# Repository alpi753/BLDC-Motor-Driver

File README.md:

# BLDC Motor Driver

Open-source BLDC ESC firmware for STM32 targets plus a desktop telemetry console. The repo contains KiCad hardware designs, two firmware builds (STM32F411 and STM32G431), and an Electron dashboard that decodes live motor data over USB.

Part of the broader [BLDC-Motor-Driver](https://github.com/alpi753/BLDC-Motor-Driver) project.

## Repository layout

```
PCB/
├── hardware/              KiCad schematics and PCBs (ESC, MCU, MOSFET boards)
├── software/
│   ├── console/           Electron + React telemetry dashboard
│   ├── stm32f411/         STM32F411CE firmware (CubeMX + CMake)
│   ├── stm32g431/         STM32G431CB firmware (CubeMX + CMake)
│   ├── shared/bsp/        Shared motor control, telemetry, USB/CBOR, DroneCAN
│   └── scripts/           Host-side utilities (e.g. telem_reader.py)
└── AGENTS.md              Contributor and AI-agent guide (architecture, protocol, gaps)
```

## Quick start

### Console (dashboard)

```bash
cd software/console
npm install
npm run dev
```

Linux USB serial access usually requires membership in the `dialout` group:

```bash
sudo usermod -a -G dialout $USER   # re-login required
```

### Firmware

Prerequisites: `arm-none-eabi-gcc`, `cmake`, `ninja` (and `openocd` for flashing).

**STM32F411**

```bash
cd software/stm32f411
cmake --preset Debug
cmake --build --preset Debug
make flash    # optional — ST-Link + OpenOCD
```

**STM32G431**

```bash
cd software/stm32g431
cmake --preset Debug
cmake --build --preset Debug
make flash
```

Select the board at configure time with `-DBLDC_BOARD=stm32f411` or `-DBLDC_BOARD=stm32g431` (default is `stm32g431` in the shared BSP CMake).

DroneCAN DSDL codegen (first build only, if `dsdl_generated/` is missing):

```bash
cd software/stm32f411   # or stm32g431
make dsdl_gen_build
```

## How it fits together

```
┌─────────────────────┐     USB CDC 115200 baud      ┌──────────────────────┐
│  STM32F411 / G431   │  CBOR [type, payload]        │  Electron main       │
│  TelemThread (~1Hz) │ ───────────────────────────► │  serial.ts decoder   │
│                     │ ◄─────────────────────────── │  ipc → React cards   │
└─────────────────────┘   settings CBOR (RX only)   └──────────────────────┘
         │
         ├── TIM1 complementary PWM → DRV8323 → 3-phase bridge
         ├── SPI1 → DRV8323R (enable, faults, gain, OC)
         └── ADC → phase currents, bus voltage, NTC temperature
```

Connect the board over USB, open the console, pick the CDC serial port, and dashboard cards update from live telemetry.

## Telemetry today

Both boards publish the same CBOR telemetry map when `CONFIG_BLDC_TELEM_USE_DEMO=n` (current default on both).

| Data | F411 | G431 |
|------|------|------|
| Phase currents (`i_a`–`i_c`) | Real — ADC1 DMA, PA0–PA2 | Real — ADC1 injected, PA0–PA2 |
| Bus voltage (`v_bat`) | Real — PA5 (`ADC1_IN5`) | Real — PB2 (`ADC2_IN12`) |
| Phase voltages (`v_a`–`v_c`) | Real — PWM duty × Vbus | Real — PWM duty × Vbus |
| FET temperature (`temp`) | Real — PA6 NTC, IIR filtered | Real — PA6 NTC, IIR + CORDIC/FMAC |
| Energy used (`e_used`) | Real — integrated V×I | Real — integrated V×I |
| Battery current (`i_bat`) | Approx — mean \|phase currents\| | Same |
| RPM, FOC (`i_d`/`i_q`), angles, observer fields | Stubbed 0 | Stubbed 0 |
| Energy remaining (`e_rem`) | Always 0 | Always 0 |
| Motor NTC (PA7) | Sampled, not telemetered | Sampled, not telemetered |

Telemetry rate is about **1 Hz** (one CBOR frame per second from `TelemThread`).

## What's not done yet

- Sensorless FOC and speed/position observers (RPM, angles, `i_d`/`i_q` stay at zero)
- Console settings UI → firmware settings over CBOR
- DroneCAN on the wire (libcanard layer exists; CAN HAL TX/RX not hooked up)
- `energy_rem` from battery capacity

For UI development without hardware, set `CONFIG_BLDC_TELEM_USE_DEMO=y` in the target's `software/shared/bsp/boards/<board>/board.conf` and rebuild.

## Documentation

- **[AGENTS.md](AGENTS.md)** — Full architecture, protocol reference, board differences, coding rules, and common tasks for contributors and AI agents.
- **[software/console/README.md](software/console/README.md)** — Console-specific setup, IPC API, and UI structure.

## License

No root-level LICENSE file is present yet. Check individual components and submodules for their terms.

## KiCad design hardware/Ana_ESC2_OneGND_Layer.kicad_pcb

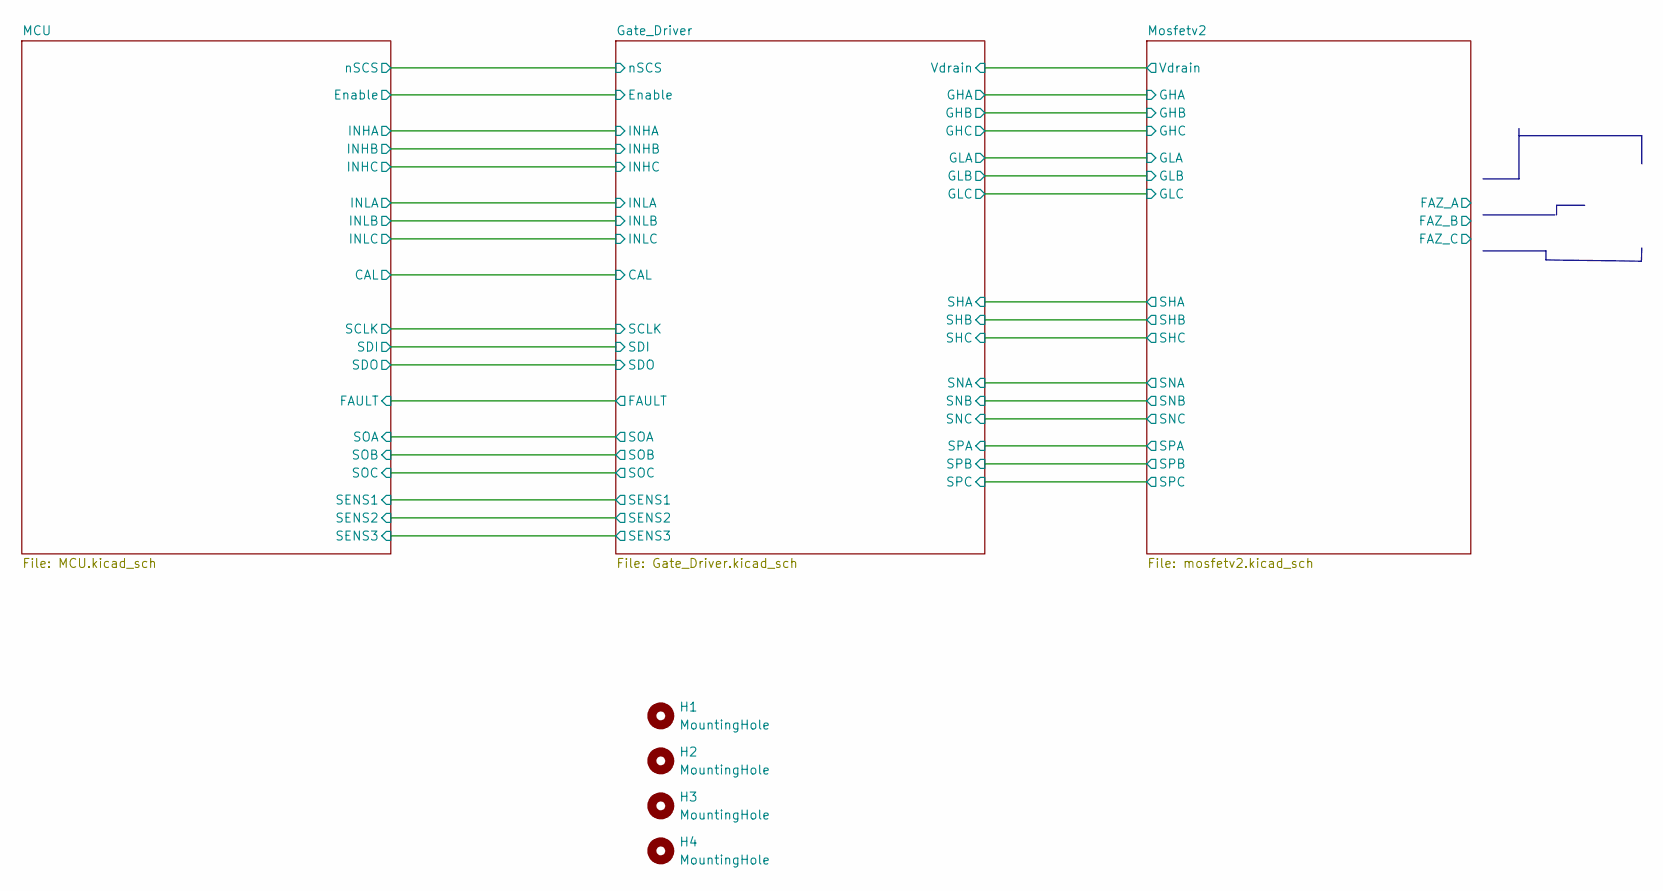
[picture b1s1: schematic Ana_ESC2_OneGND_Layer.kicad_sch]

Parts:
H1, H2, H3, H4: MountingHole; MountingHole_3.2mm_M3

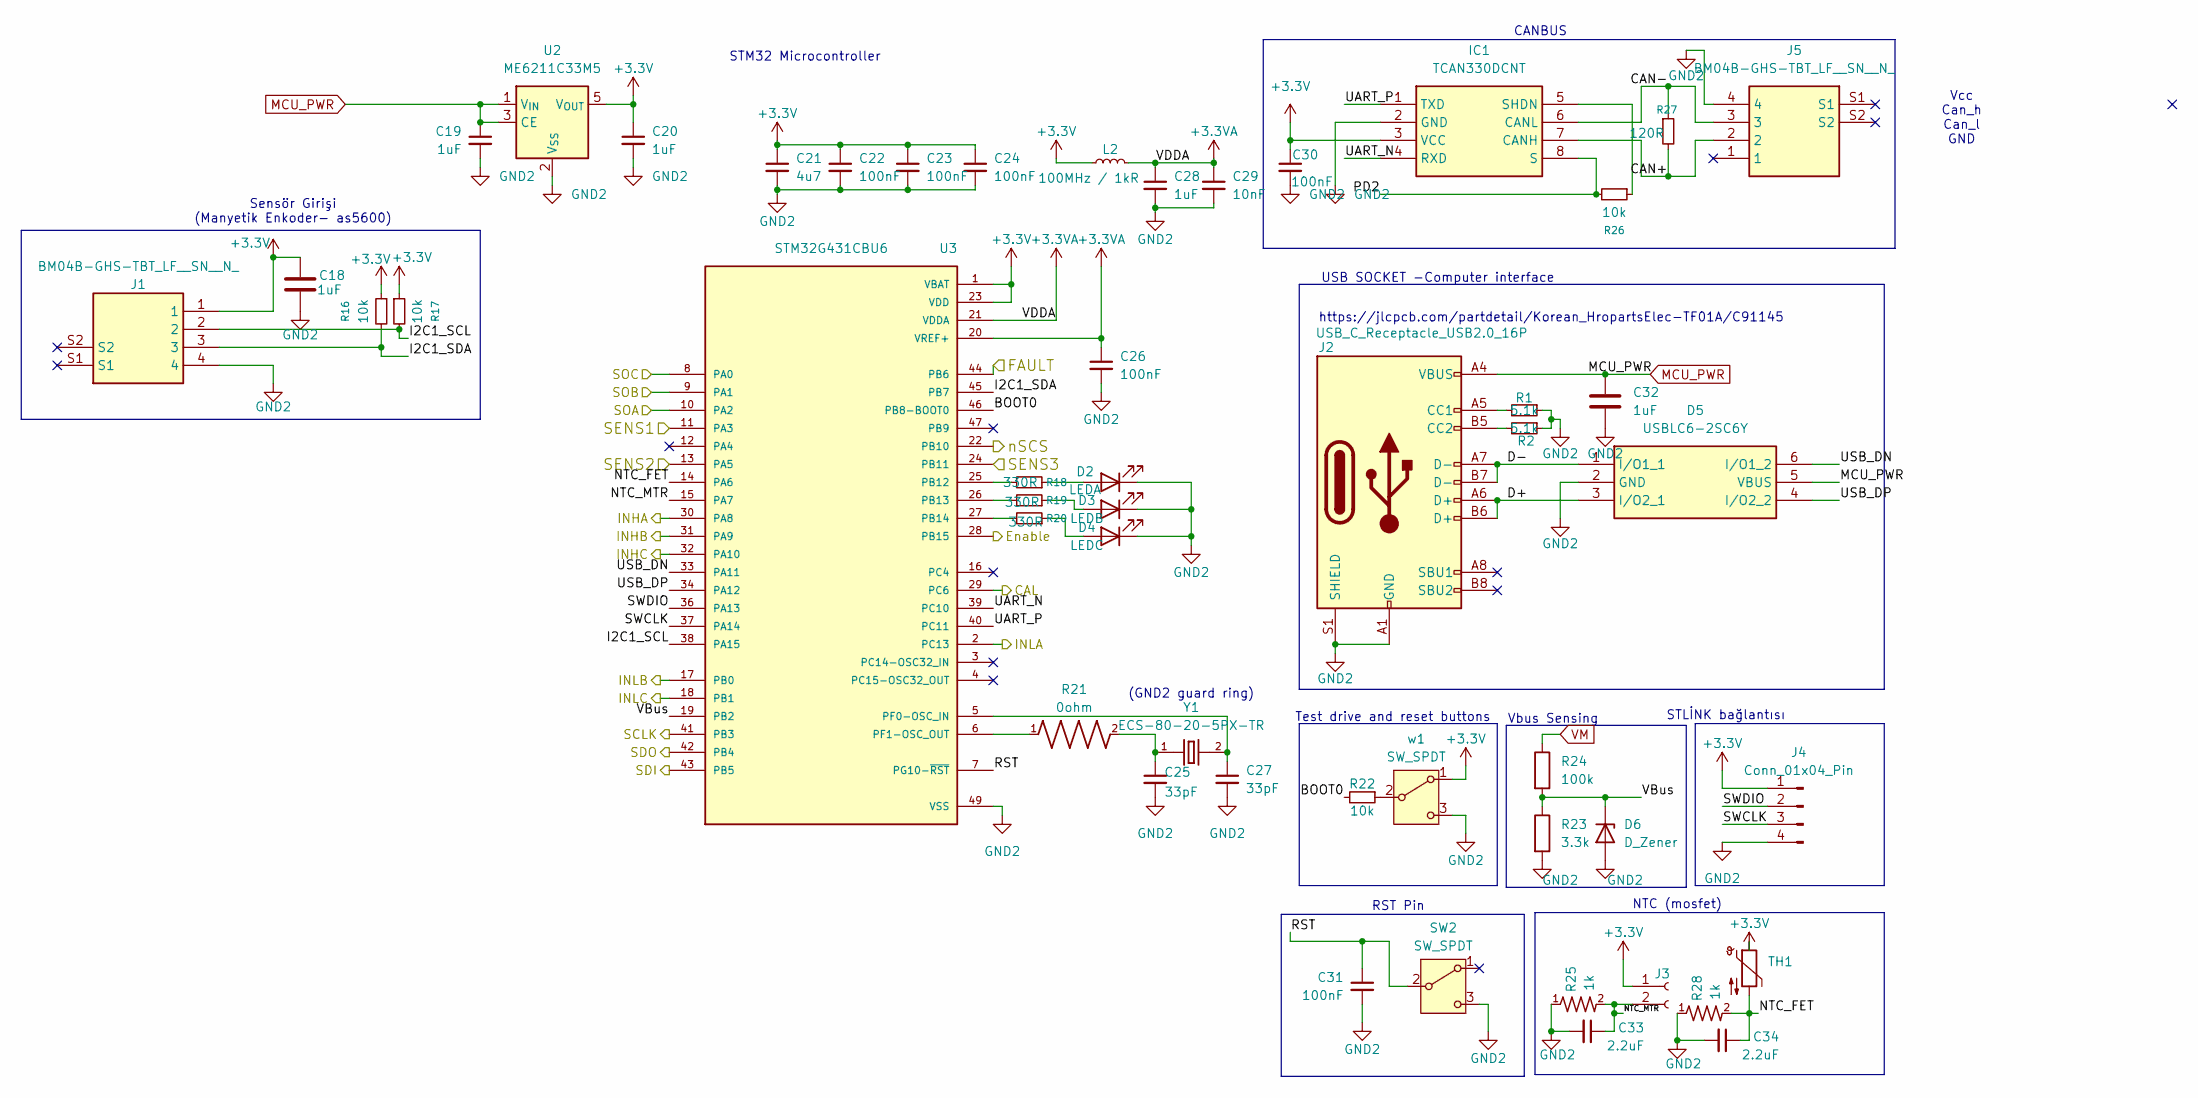
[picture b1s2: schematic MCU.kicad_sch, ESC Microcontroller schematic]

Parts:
C18, C32: 1uF; C_0603_1608Metric_Pad1.08x0.95mm_HandSolder
C19, C20, C28: 1uF; C_0603_1608Metric_Pad1.08x0.95mm_HandSolder; LCSC Part # C52923
C21: 4u7; C_0603_1608Metric_Pad1.08x0.95mm_HandSolder; LCSC Part # C19666
C22, C23, C24, C26, C31: 100nF; C_0603_1608Metric_Pad1.08x0.95mm_HandSolder; LCSC Part # C1525
C25, C27: 33pF; C_0603_1608Metric_Pad1.08x0.95mm_HandSolder
C29: 10nF; C_0603_1608Metric_Pad1.08x0.95mm_HandSolder; LCSC Part # C15195
C30: 100nF; C_0603_1608Metric_Pad1.08x0.95mm_HandSolder
C33, C34: 2.2uF; C_0603_1608Metric_Pad1.08x0.95mm_HandSolder
D2: LEDA; LED_0603_1608Metric_Pad1.05x0.95mm_HandSolder
D3: LEDB; LED_0603_1608Metric_Pad1.05x0.95mm_HandSolder
D4: LEDC; LED_0603_1608Metric_Pad1.05x0.95mm_HandSolder
D5: USBLC6-2SC6Y; SOT95P280X145-6N; Manufacturer_Part_Number USBLC6-2SC6Y; Mouser Part Number 511-USBLC6-2SC6Y
D6: D_Zener; SOD3716X135N
IC1: TCAN330DCNT; SOT65P280X145-8N; Manufacturer_Part_Number TCAN330DCNT; Mouser Part Number 595-TCAN330DCNT
J1, J5: BM04B-GHS-TBT_LF__SN__N_; JST_BM04B-GHS-TBT_LF__SN__N_; Manufacturer_Part_Number BM04B-GHS-TBT(LF)(SN)(N); Mouser Part Number N/A
J2: USB_C_Receptacle_USB2.0_16P; USB_C_Receptacle_GCT_USB4105-xx-A_16P_TopMnt_Horizontal
J3: Conn_01x02_Socket; TerminalBlock_MaiXu_MX126-5.0-02P_1x02_P5.00mm
J4: Conn_01x04_Pin; PinHeader_1x04_P1.00mm_Vertical
L2: 100MHz / 1kR; L_0603_1608Metric_Pad1.05x0.95mm_HandSolder; LCSC Part # C26443
R1, R2: 5.1k; R_0603_1608Metric_Pad0.98x0.95mm_HandSolder; LCSC Part # C25744
R16, R17, R26: 10k; R_0603_1608Metric_Pad0.98x0.95mm_HandSolder
R18, R19, R20: 330R; R_0603_1608Metric_Pad0.98x0.95mm_HandSolder
R21: 0ohm; RESC1508X55N
R22: 10k; R_0603_1608Metric_Pad0.98x0.95mm_HandSolder; LCSC Part # C25744
R23: 3.3k; R_0603_1608Metric_Pad0.98x0.95mm_HandSolder
R24: 100k; R_0603_1608Metric_Pad0.98x0.95mm_HandSolder
R25, R28: 1k; R_0603_1608Metric_Pad0.98x0.95mm_HandSolder; DigiKey_Part_Number RNCP0603FTD1K00CT-ND
R27: 120R; R_0603_1608Metric_Pad0.98x0.95mm_HandSolder
SW2: SW_SPDT; SW_SPDT_PCM12
TH1: ERT-J1VG103FA; R_0603_1608Metric
U2: ME6211C33M5; SOT-23-5
U3: STM32G431CBU6; QFN50P700X700X60-49N; PARTREV 6
Y1: ECS-80-20-5PX-TR; XTAL_ECS-80-20-5PX-TR; PARTREV 2017
w1: SW_SPDT; SW_SPDT_PCM12

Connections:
+3.3V: C18.1, C20.1, C21.1, C22.1, C23.1, C24.1, C30.1, IC1.3 (VCC), J1.1, J3.1, J4.1, L2.1, R16.1, R17.1, TH1.1, U2.5 (V_{OUT}), U3.1 (VBAT), U3.23 (VDD), U3.35 (VDD), U3.48 (VDD), w1.1 (A); also elsewhere on the board
+3.3VA: C26.1, C28.1, C29.1, L2.2, U3.20 (VREF+), U3.21 (VDDA)
/Gate_Driver/CAL: U3.29 (PC6); also elsewhere on the board
/Gate_Driver/Enable: U3.28 (PB15); also elsewhere on the board
/Gate_Driver/INHA: U3.30 (PA8); also elsewhere on the board
/Gate_Driver/INHB: U3.31 (PA9); also elsewhere on the board
/Gate_Driver/INHC: U3.32 (PA10); also elsewhere on the board
/Gate_Driver/INLA: U3.2 (PC13); also elsewhere on the board
/Gate_Driver/INLB: U3.17 (PB0); also elsewhere on the board
/Gate_Driver/INLC: U3.18 (PB1); also elsewhere on the board
/Gate_Driver/SCLK: U3.41 (PB3); also elsewhere on the board
/Gate_Driver/SDI: U3.43 (PB5); also elsewhere on the board
/Gate_Driver/SENS1: U3.11 (PA3); also elsewhere on the board
/Gate_Driver/SENS2: U3.13 (PA5); also elsewhere on the board
/Gate_Driver/SENS3: U3.24 (PB11); also elsewhere on the board
/Gate_Driver/SOA: U3.10 (PA2); also elsewhere on the board
/Gate_Driver/SOB: U3.9 (PA1); also elsewhere on the board
/Gate_Driver/SOC: U3.8 (PA0); also elsewhere on the board
/Gate_Driver/nSCS: U3.22 (PB10); also elsewhere on the board
/MCU/BOOT0: R22.2, U3.46 (PB8-BOOT0)
/MCU/CAN+: IC1.7 (CANH), J5.2, R27.2
/MCU/CAN-: IC1.6 (CANL), J5.3, R27.1
/MCU/D+: D5.3 (I/O2_1), J2.A6 (D+), J2.B6 (D+)
/MCU/D-: D5.1 (I/O1_1), J2.A7 (D-), J2.B7 (D-)
/MCU/I2C1_SCL: J1.2, R17.2, U3.38 (PA15)
/MCU/I2C1_SDA: J1.3, R16.2, U3.45 (PB7)
/MCU/NTC_FET: C34.1, R28.2, TH1.2, U3.14 (PA6)
/MCU/NTC_MTR: C33.1, J3.2, R25.2, U3.15 (PA7)
/MCU/PD2: IC1.8 (S), R26.2
/MCU/RST: C31.1, SW2.2 (B), U3.7 (PG10-~RST)
/MCU/SWCLK: J4.3, U3.37 (PA14)
/MCU/SWDIO: J4.2, U3.36 (PA13)
/MCU/UART_N: IC1.4 (RXD), U3.39 (PC10)
/MCU/UART_P: IC1.1 (TXD), U3.40 (PC11)
/MCU/USB_DN: D5.6 (I/O1_2), U3.33 (PA11)
/MCU/USB_DP: D5.4 (I/O2_2), U3.34 (PA12)
MCU_PWR: C19.1, C32.1, D5.5 (VBUS), J2.A4 (VBUS), J2.A9 (VBUS), J2.B4 (VBUS), J2.B9 (VBUS), U2.1 (V_{IN}), U2.3 (CE); also elsewhere on the board
unnamed: C25.1, R21.2, Y1.1
unnamed: D2.2 (A), R18.1
unnamed: D3.2 (A), R19.1
unnamed: D4.2 (A), R20.1
unnamed: IC1.5 (SHDN), R26.1
unnamed: J2.A5 (CC1), R1.2
unnamed: J2.B5 (CC2), R2.2
unnamed: R18.2, U3.25 (PB12)
unnamed: R19.2, U3.26 (PB13)
unnamed: R20.2, U3.27 (PB14)
unnamed: C27.1, U3.5 (PF0-OSC_IN), Y1.2
unnamed: R21.1, U3.6 (PF1-OSC_OUT)
unnamed: R22.1, w1.2 (B)
VM: R24.1; also elsewhere on the board

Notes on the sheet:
STM32 Microcontroller
Test drive and reset buttons
NTC (mosfet)
(GND2 guard ring)
Sensör Girişi (Manyetik Enkoder- as5600)
STLİNK bağlantısı
CANBUS
https://jlcpcb.com/partdetail/Korean_HropartsElec-TF01A/C91145
USB SOCKET -Computer interface
RST Pin
Vcc Can_h Can_l GND
Vbus Sensing

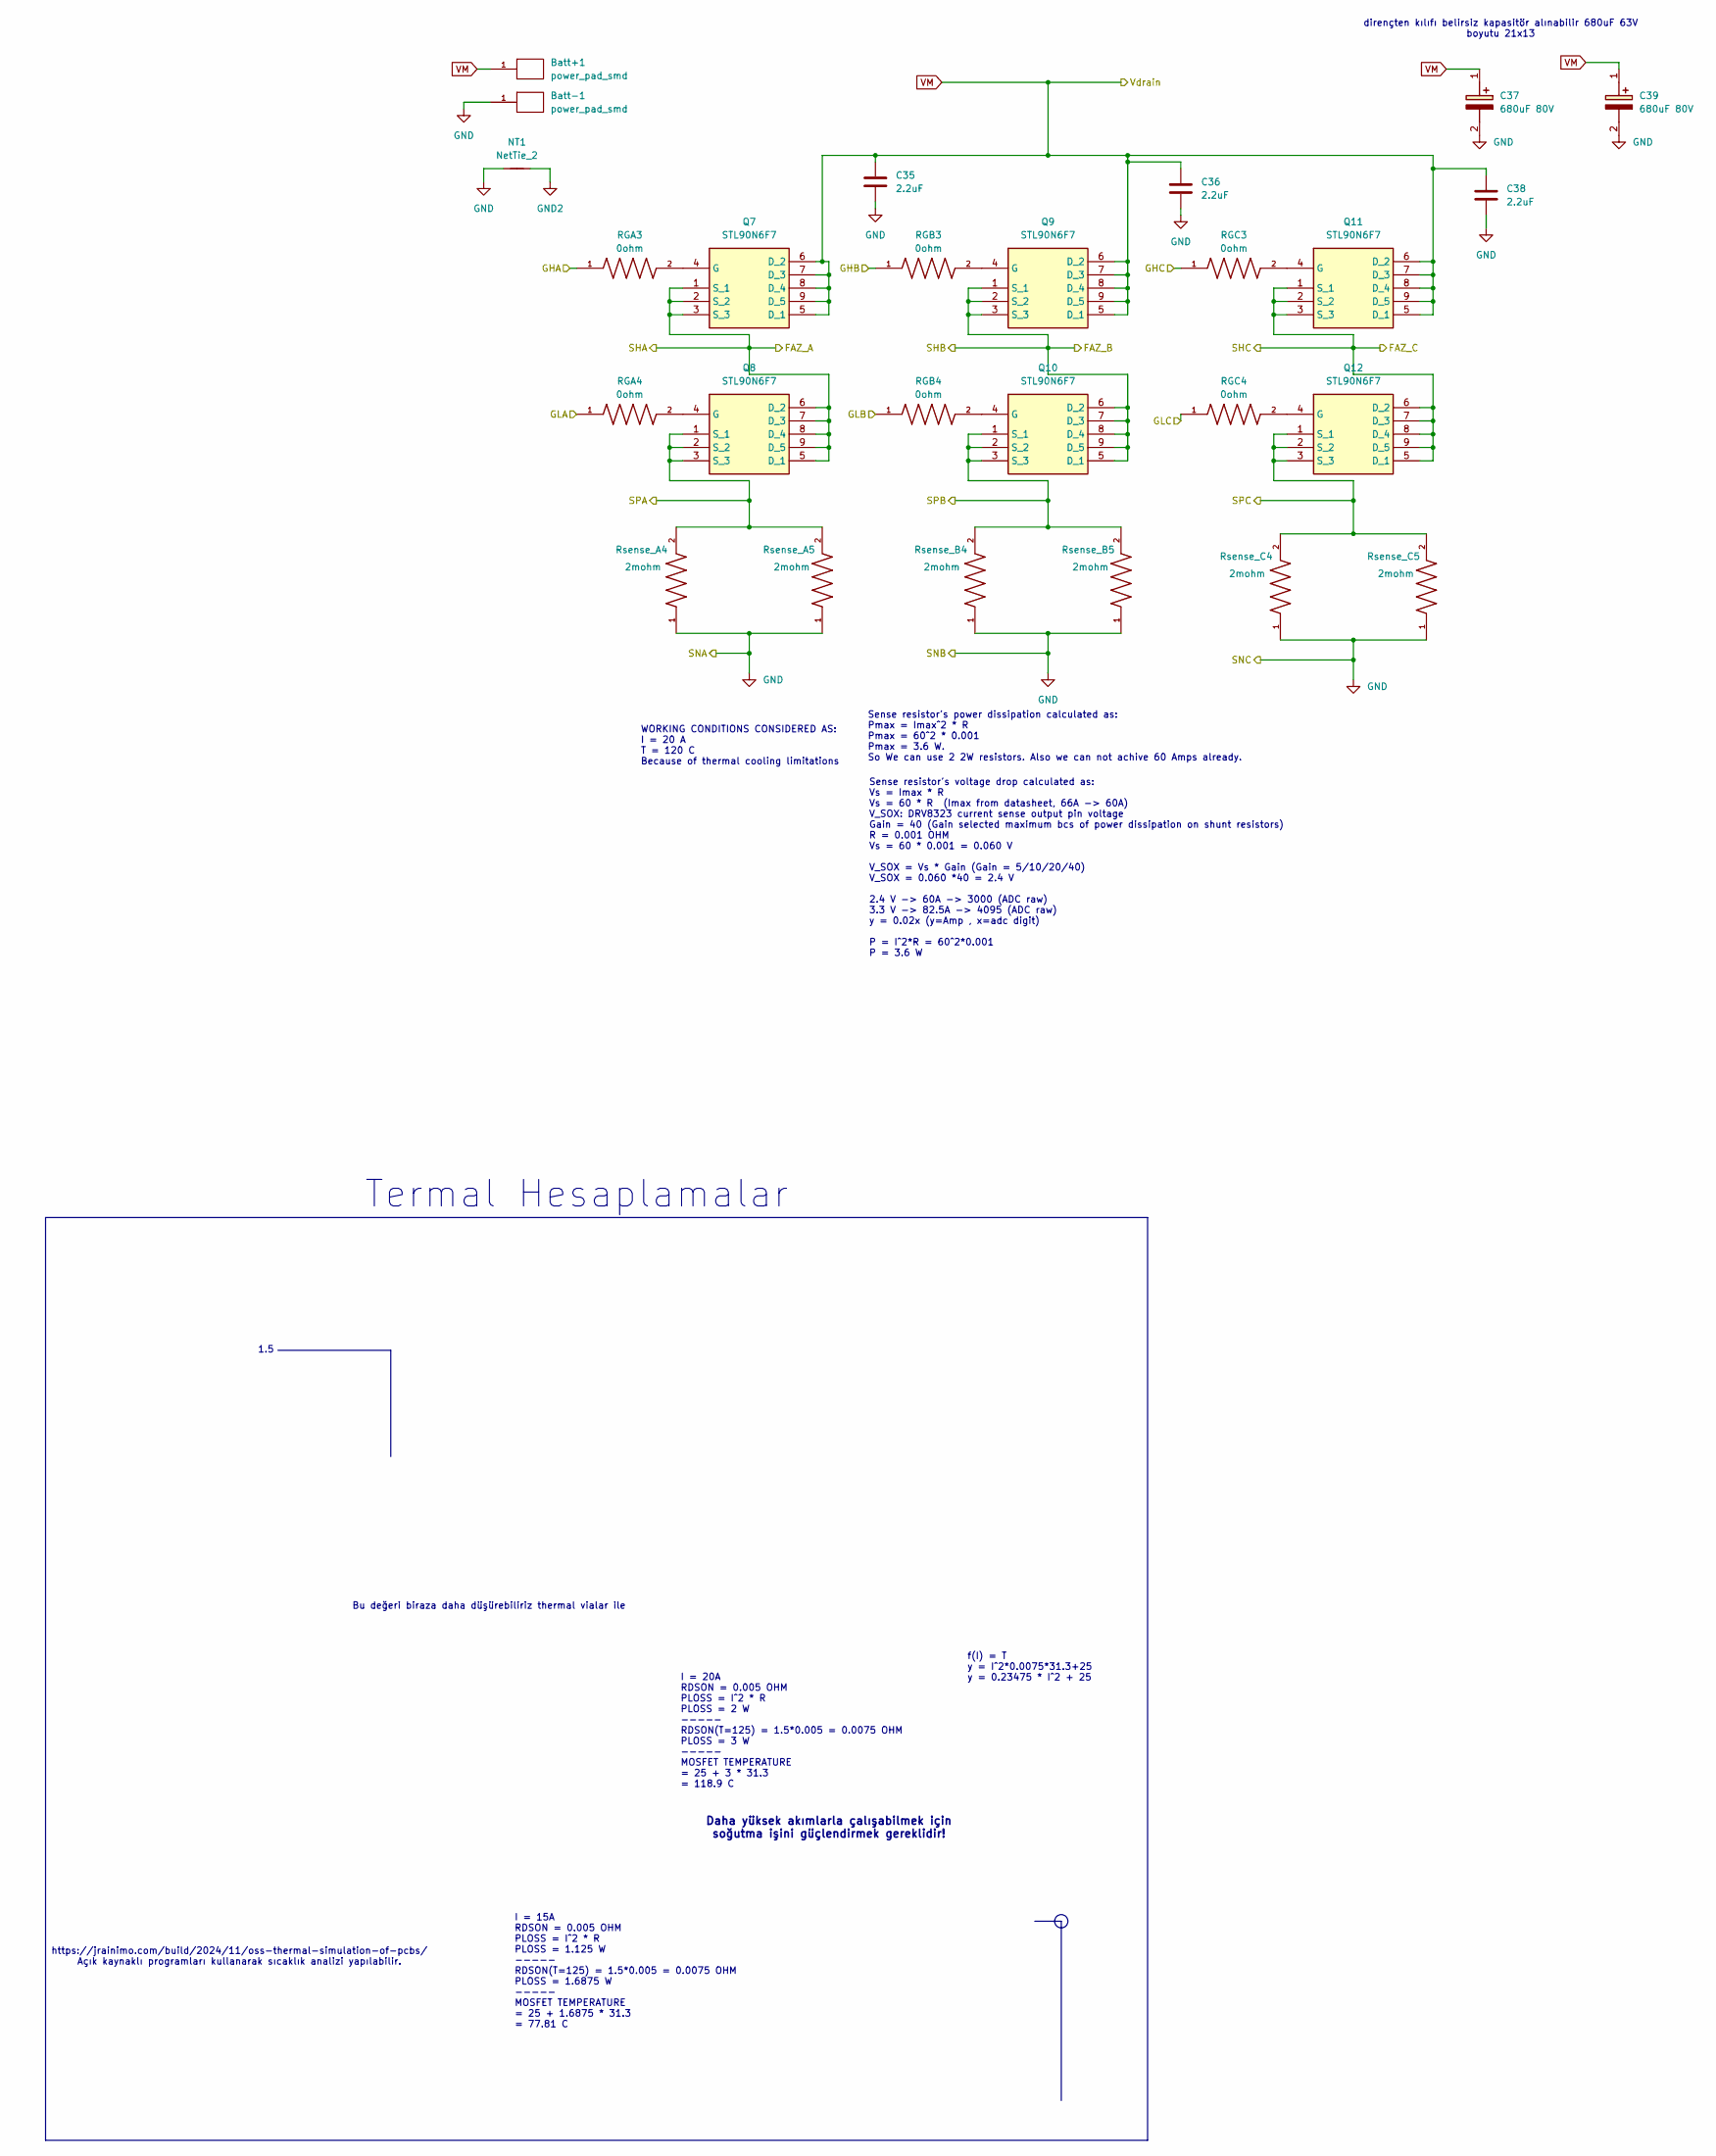
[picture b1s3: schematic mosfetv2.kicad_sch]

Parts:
Batt+1: power_pad_smd; Power_pad_smd
Batt-1: power_pad_smd; Power_pad_smd
C35, C36, C38: 2.2uF; C_0603_1608Metric_Pad1.08x0.95mm_HandSolder
C37, C39: 680uF 80V; CAPPRD750W85D1600H2700; Manufacturer_Part_Number EEUFS1K681
NT1: NetTie_2; NetTie-2_THT_Pad0.3mm
Q7, Q8, Q9, Q10, Q11, Q12: STL90N6F7; STL90N6F7_Thermal_Vias; Manufacturer_Part_Number STL90N6F7; Mouser Part Number 511-STL90N6F7
RGA3, RGA4: 0ohm; RESC1508X55N
RGB3, RGB4: 0ohm; RESC1508X55N
RGC3, RGC4: 0ohm; RESC1508X55N
Rsense_A4, Rsense_A5: 2mohm; RESC6432X80N
Rsense_B4, Rsense_B5: 2mohm; RESC6432X80N
Rsense_C4, Rsense_C5: 2mohm; RESC6432X80N

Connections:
/Gate_Driver/GHA: RGA3.1; also elsewhere on the board
/Gate_Driver/GHB: RGB3.1; also elsewhere on the board
/Gate_Driver/GHC: RGC3.1; also elsewhere on the board
/Gate_Driver/GLA: RGA4.1; also elsewhere on the board
/Gate_Driver/GLB: RGB4.1; also elsewhere on the board
/Gate_Driver/GLC: RGC4.1; also elsewhere on the board
/Gate_Driver/SHA: Q7.1 (S_1), Q7.2 (S_2), Q7.3 (S_3), Q8.5 (D_1), Q8.6 (D_2), Q8.7 (D_3), Q8.8 (D_4), Q8.9 (D_5); also elsewhere on the board
/Gate_Driver/SHB: Q9.1 (S_1), Q9.2 (S_2), Q9.3 (S_3), Q10.5 (D_1), Q10.6 (D_2), Q10.7 (D_3), Q10.8 (D_4), Q10.9 (D_5); also elsewhere on the board
/Gate_Driver/SHC: Q11.1 (S_1), Q11.2 (S_2), Q11.3 (S_3), Q12.5 (D_1), Q12.6 (D_2), Q12.7 (D_3), Q12.8 (D_4), Q12.9 (D_5); also elsewhere on the board
/Gate_Driver/SPA: Q8.1 (S_1), Q8.2 (S_2), Q8.3 (S_3), Rsense_A4.2, Rsense_A5.2; also elsewhere on the board
/Gate_Driver/SPB: Q10.1 (S_1), Q10.2 (S_2), Q10.3 (S_3), Rsense_B4.2, Rsense_B5.2; also elsewhere on the board
/Gate_Driver/SPC: Q12.1 (S_1), Q12.2 (S_2), Q12.3 (S_3), Rsense_C4.2, Rsense_C5.2; also elsewhere on the board
unnamed: Q7.4 (G), RGA3.2
unnamed: Q8.4 (G), RGA4.2
unnamed: Q9.4 (G), RGB3.2
unnamed: Q10.4 (G), RGB4.2
unnamed: Q11.4 (G), RGC3.2
unnamed: Q12.4 (G), RGC4.2
VM: Batt+1.1, C35.1, C36.1, C37.1 (+), C38.1, C39.1 (+), Q7.5 (D_1), Q7.6 (D_2), Q7.7 (D_3), Q7.8 (D_4), Q7.9 (D_5), Q9.5 (D_1), Q9.6 (D_2), Q9.7 (D_3), Q9.8 (D_4), Q9.9 (D_5), Q11.5 (D_1), Q11.6 (D_2), Q11.7 (D_3), Q11.8 (D_4), Q11.9 (D_5); also elsewhere on the board

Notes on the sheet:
https://jrainimo.com/build/2024/11/oss-thermal-simulation-of-pcbs/ Açık kaynaklı programları kullanarak sıcaklık analizi yapılabilir.
Daha yüksek akımlarla çalışabilmek için soğutma işini güçlendirmek gereklidir!
I = 20A RDSON = 0.005 OHM PLOSS = I^2 * R PLOSS = 2 W ----- RDSON(T=125) = 1.5*0.005 = 0.0075 OHM PLOSS = 3 W ----- MOSFET TEMPERATURE = 25 + 3 * 31.3 = 118.9 C
1.5
f(I) = T y = I^2*0.0075*31.3+25 y = 0.23475 * I^2 + 25
Sense resistor's power dissipation calculated as: Pmax = Imax^2 * R Pmax = 60^2 * 0.001 Pmax = 3.6 W. So We can use 2 2W resistors. Also we can not achive 60 Amps already.
Termal Hesaplamalar
dirençten kılıfı belirsiz kapasitör alınabilir 680uF 63V boyutu 21x13
Sense resistor's voltage drop calculated as: Vs = Imax * R Vs = 60 * R (Imax from datasheet, 66A -> 60A) V_SOX: DRV8323 current sense output pin voltage Gain = 40 (Gain selected maximum bcs of power dissipation on shunt resistors) R = 0.001 OHM Vs = 60 * 0.001 = 0.060 V V_SOX = Vs * Gain (Gain = 5/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
WORKING CONDITIONS CONSIDERED AS: I = 20 A T = 120 C Because of thermal cooling limitations
I = 15A RDSON = 0.005 OHM PLOSS = I^2 * R PLOSS = 1.125 W ----- RDSON(T=125) = 1.5*0.005 = 0.0075 OHM PLOSS = 1.6875 W ----- MOSFET TEMPERATURE = 25 + 1.6875 * 31.3 = 77.81 C
Bu değeri biraza daha düşürebiliriz thermal vialar ile

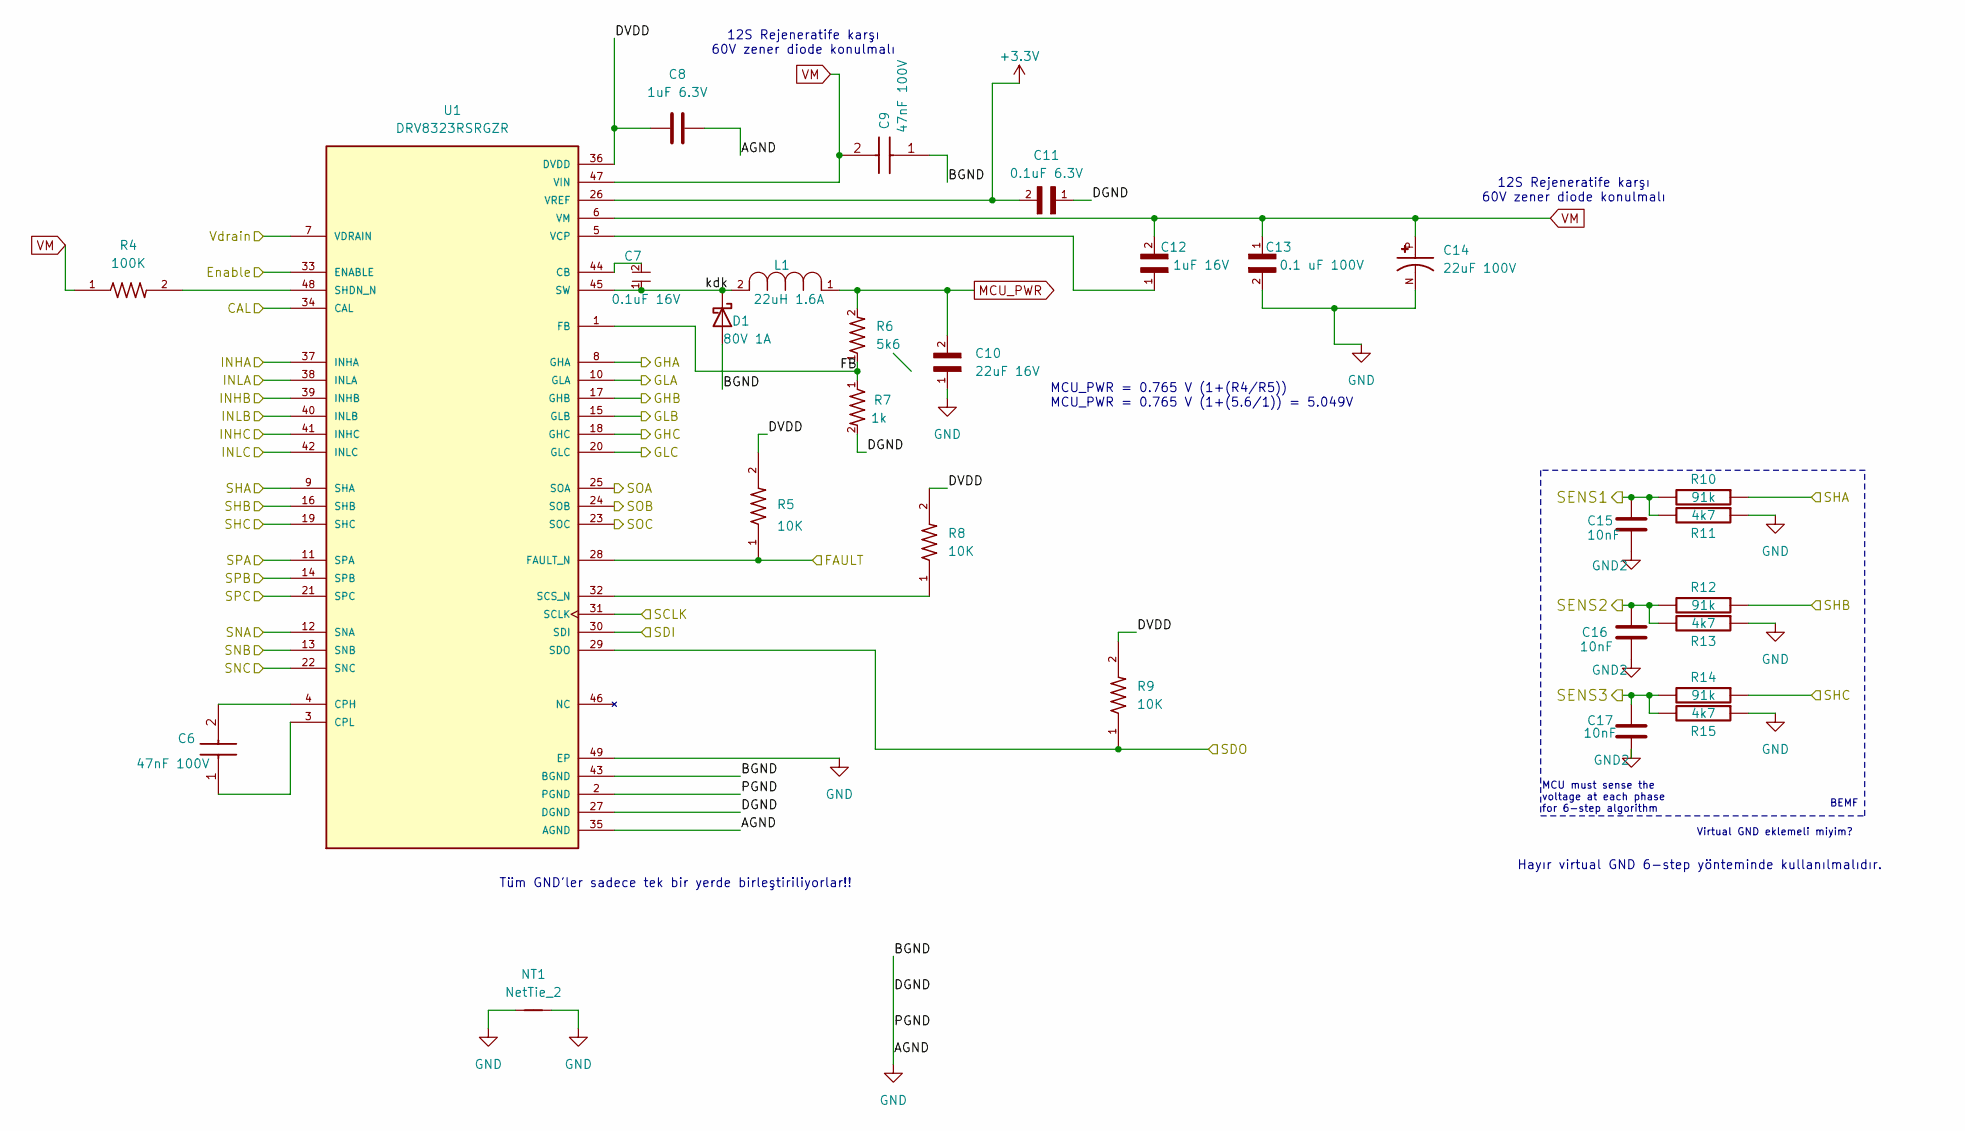
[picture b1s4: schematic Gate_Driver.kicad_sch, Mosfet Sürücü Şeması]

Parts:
C6, C9: 47nF 100V; C_0805_2012Metric_Pad1.18x1.45mm_HandSolder; Manufacturer_Part_Number C0805C473K1RECAUTO; Mouser Part Number 80-C0805C473K1RECAUT
C7: 0.1uF 16V; C_0603_1608Metric_Pad1.08x0.95mm_HandSolder
C8: 1uF 6.3V; C_0603_1608Metric_Pad1.08x0.95mm_HandSolder
C10: 22uF 16V; C_0805_2012Metric_Pad1.18x1.45mm_HandSolder
C11: 0.1uF 6.3V; CAPC2012X140N
C12: 1uF 16V; CAPC1608X90N; PARTREV 2/20/2025
C13: 0.1 uF 100V; CAPC1608X90N
C14: 22uF 100V; CAPPRD500W50D630H1120; PARTREV 20-DEC-19; DigiKey_Part_Number 10-ECA-2AM220BCT-ND
C15, C16, C17: 10nF; C_0603_1608Metric_Pad1.08x0.95mm_HandSolder
D1: 80V 1A; D_SMA
L1: 22uH 1.6A; INDM7676X355N; TOLERANCE ±20%; MPN DR73-220-R
NT1: NetTie_2
R4: 100K; RESC1607X60N
R5, R8, R9: 10K; RESC1607X60N
R6: 5k6; RESC1607X60N
R7: 1k; RESC1508X50N; DigiKey_Part_Number RNCP0603FTD1K00CT-ND
R10, R12, R14: 91k; R_0603_1608Metric_Pad0.98x0.95mm_HandSolder
R11, R13, R15: 4k7; R_0603_1608Metric_Pad0.98x0.95mm_HandSolder
U1: DRV8323RSRGZR; QFN50P700X700X100-49N; PARTREV C

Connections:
+3.3V: C11.2, U1.26 (VREF); also elsewhere on the board
/Gate_Driver/CAL: U1.34 (CAL); also elsewhere on the board
/Gate_Driver/Enable: U1.33 (ENABLE); also elsewhere on the board
/Gate_Driver/FB: R6.1, R7.1, U1.1 (FB)
/Gate_Driver/GHA: U1.8 (GHA); also elsewhere on the board
/Gate_Driver/GHB: U1.17 (GHB); also elsewhere on the board
/Gate_Driver/GHC: U1.18 (GHC); also elsewhere on the board
/Gate_Driver/GLA: U1.10 (GLA); also elsewhere on the board
/Gate_Driver/GLB: U1.15 (GLB); also elsewhere on the board
/Gate_Driver/GLC: U1.20 (GLC); also elsewhere on the board
/Gate_Driver/INHA: U1.37 (INHA); also elsewhere on the board
/Gate_Driver/INHB: U1.39 (INHB); also elsewhere on the board
/Gate_Driver/INHC: U1.41 (INHC); also elsewhere on the board
/Gate_Driver/INLA: U1.38 (INLA); also elsewhere on the board
/Gate_Driver/INLB: U1.40 (INLB); also elsewhere on the board
/Gate_Driver/INLC: U1.42 (INLC); also elsewhere on the board
/Gate_Driver/SCLK: U1.31 (SCLK); also elsewhere on the board
/Gate_Driver/SDI: U1.30 (SDI); also elsewhere on the board
/Gate_Driver/SENS1: C15.1, R10.2, R11.2; also elsewhere on the board
/Gate_Driver/SENS2: C16.1, R12.2, R13.2; also elsewhere on the board
/Gate_Driver/SENS3: C17.1, R14.2, R15.2; also elsewhere on the board
/Gate_Driver/SHA: R10.1, U1.9 (SHA); also elsewhere on the board
/Gate_Driver/SHB: R12.1, U1.16 (SHB); also elsewhere on the board
/Gate_Driver/SHC: R14.1, U1.19 (SHC); also elsewhere on the board
/Gate_Driver/SOA: U1.25 (SOA); also elsewhere on the board
/Gate_Driver/SOB: U1.24 (SOB); also elsewhere on the board
/Gate_Driver/SOC: U1.23 (SOC); also elsewhere on the board
/Gate_Driver/SPA: U1.11 (SPA); also elsewhere on the board
/Gate_Driver/SPB: U1.14 (SPB); also elsewhere on the board
/Gate_Driver/SPC: U1.21 (SPC); also elsewhere on the board
/Gate_Driver/kdk: C7.1, D1.1 (K), L1.2, U1.45 (SW)
/Gate_Driver/nSCS: R8.1, U1.32 (SCS_N); also elsewhere on the board
MCU_PWR: C10.2, L1.1, R6.2; also elsewhere on the board
unnamed: C7.2, U1.44 (CB)
unnamed: C6.2, U1.4 (CPH)
unnamed: C6.1, U1.3 (CPL)
unnamed: R4.2, U1.48 (SHDN_N)
unnamed: C12.1, U1.5 (VCP)
VM: C9.2, C12.2, C13.1, C14.1 (+), C14.P, R4.1, U1.6 (VM), U1.7 (VDRAIN), U1.47 (VIN); also elsewhere on the board

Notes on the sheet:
MCU_PWR = 0.765 V (1+(R4/R5)) MCU_PWR = 0.765 V (1+(5.6/1)) = 5.049V
Hayır virtual GND 6-step yönteminde kullanılmalıdır.
MCU must sense the voltage at each phase for 6-step algorithm
BEMF
Tüm GND'ler sadece tek bir yerde birleştiriliyorlar!!
12S Rejeneratife karşı 60V zener diode konulmalı
Virtual GND eklemeli miyim?

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
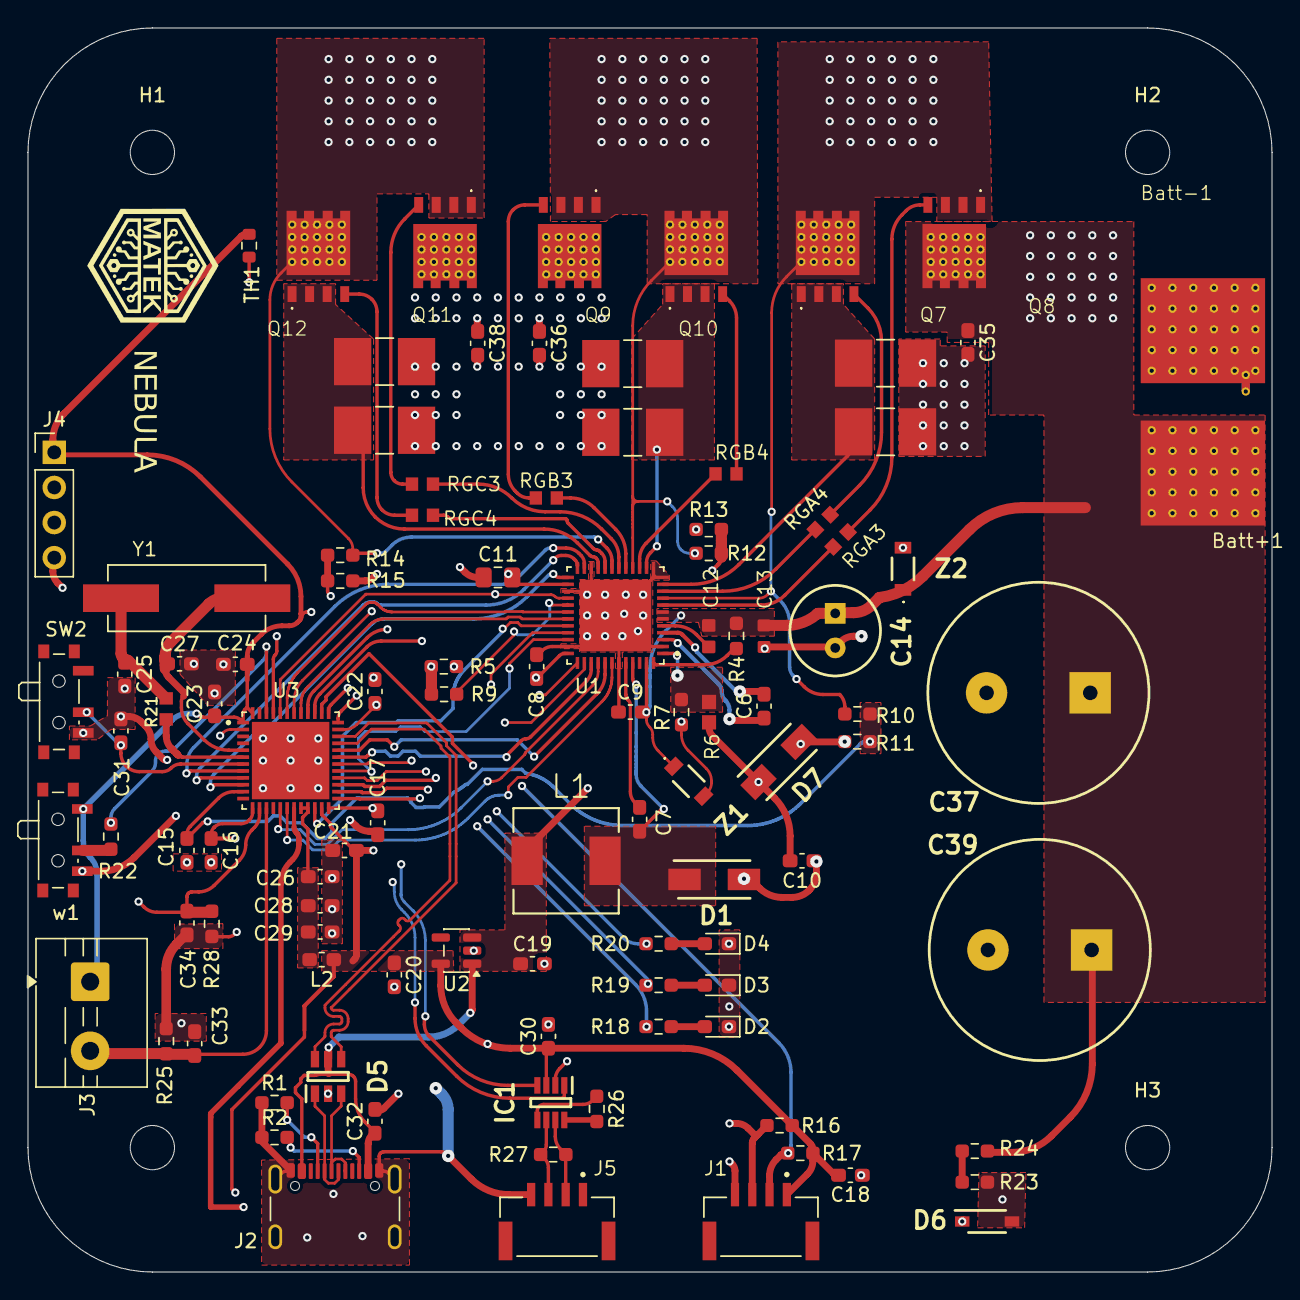
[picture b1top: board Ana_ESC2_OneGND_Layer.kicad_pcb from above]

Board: 4 copper layers, 90.0 x 90.0 mm, 109 parts (0 on the bottom side), 83 nets.

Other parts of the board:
D7: SMAJ5.0A-E3_61; DIOM5127X229N
Z1, Z2: KDZLVTR56

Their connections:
MCU_PWR: D7.1 (K); also elsewhere on the board
VM: Z1.1 (K), Z2.1 (K); also elsewhere on the board

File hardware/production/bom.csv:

Designator,Footprint,Quantity,Value,LCSC Part #
"BATT+1, BATT-1",Power_pad_smd,2,power_pad_smd,
C10,0603,1,22uF 16V,
C11,0805,1,0.1uF 6.3V,
C12,CAPC1608X90N,1,1uF 16V,
C13,CAPC1608X90N,1,0.1 uF 100V,
C14,CAPPRD250W50D655H1250,1,22uF 100V,
"C15, C16, C17",0603,3,10nF,
"C18, C32",0603,2,1uF,
"C19, C20, C28",0603,3,1uF,C52923
C21,0603,1,4u7,C19666
"C22, C23, C24, C26, C31",0603,5,100nF,C1525
"C25, C27",0603,2,33pF,
C29,0603,1,10nF,C15195
C30,0603,1,100nF,
"C33, C34, C35, C36, C38",0603,5,2.2uF,
"C37, C39",CAPPRD750W85D1600H2700,2,680uF 80V,
"C6, C9",0603,2,47nF 100V,
C7,0603,1,0.1uF 16V,
C8,0603,1,1uF 6.3V,
D1,DIOM5227X270N,1,SS18 80V 1A,
D2,0603,1,LEDA,
D3,0603,1,LEDB,
D4,0603,1,LEDC,
D5,SOT95P280X145-6N,1,USBLC6-2SC6Y,
D6,SOD3716X135N,1,D_Zener,
D7,DIOM5127X229N,1,SMAJ5.0A-E3_61,
IC1,SOT65P280X145-8N,1,TCAN330DCNT,
"J1, J5",JST_BM04B-GHS-TBT_LF__SN__N_,2,BM04B-GHS-TBT_LF__SN__N_,
J2,USB_C_Receptacle_GCT_USB4105-xx-A_16P_TopMnt_Horizontal,1,USB_C_Receptacle_USB2.0_16P,
J3,TerminalBlock_MaiXu_MX126-5.0-02P_1x02_P5.00mm,1,Conn_01x02_Socket,
J4,PinHeader_1x04_P2.54mm_Vertical,1,Conn_01x04_Pin,
L1,INDM7676X355N,1,22uH 1.6A,DR73-220-R
L2,0603,1,100MHz / 1kR,C26443
"Q10, Q11, Q12, Q7, Q8, Q9",STL90N6F7_Thermal_Vias,6,STL90N6F7,
"R1, R2",0603,2,5.1k,C25744
"R10, R12, R14",0603,3,91k,
"R11, R13, R15",0603,3,4k7,
"R16, R17, R26, R5, R9",0603,5,10k,
"R18, R19, R20",0603,3,330R,
"R21, RGA3, RGA4, RGB3, RGB4, RGC3, RGC4",RESC1508X55N,7,0ohm,
R22,0603,1,10k,C25744
R23,0603,1,3.3k,
"R24, R4",0603,2,100k,
"R25, R28, R7",0603,3,1k,
R27,0603,1,120R,
R6,RESC1607X60N,1,5k6,
"RSENSE_A4, RSENSE_A5, RSENSE_B4, RSENSE_B5, RSENSE_C4, RSENSE_C5",RESC6432X80N,6,2mohm,
"SW2, W1",SW_SPDT_PCM12,2,SW_SPDT,
TH1,0603,1,ERT-J1VG103FA,
U1,QFN50P700X700X100-49N,1,DRV8323RSRGZR,
U2,SOT-23-5,1,ME6211C33M5,
U3,QFN50P700X700X60-49N,1,STM32G431CBU6,
Y1,XTAL_ECS-80-20-5PX-TR,1,ECS-80-20-5PX-TR,
"Z1, Z2",KDZLVTR56,2,KDZLVTR56,
